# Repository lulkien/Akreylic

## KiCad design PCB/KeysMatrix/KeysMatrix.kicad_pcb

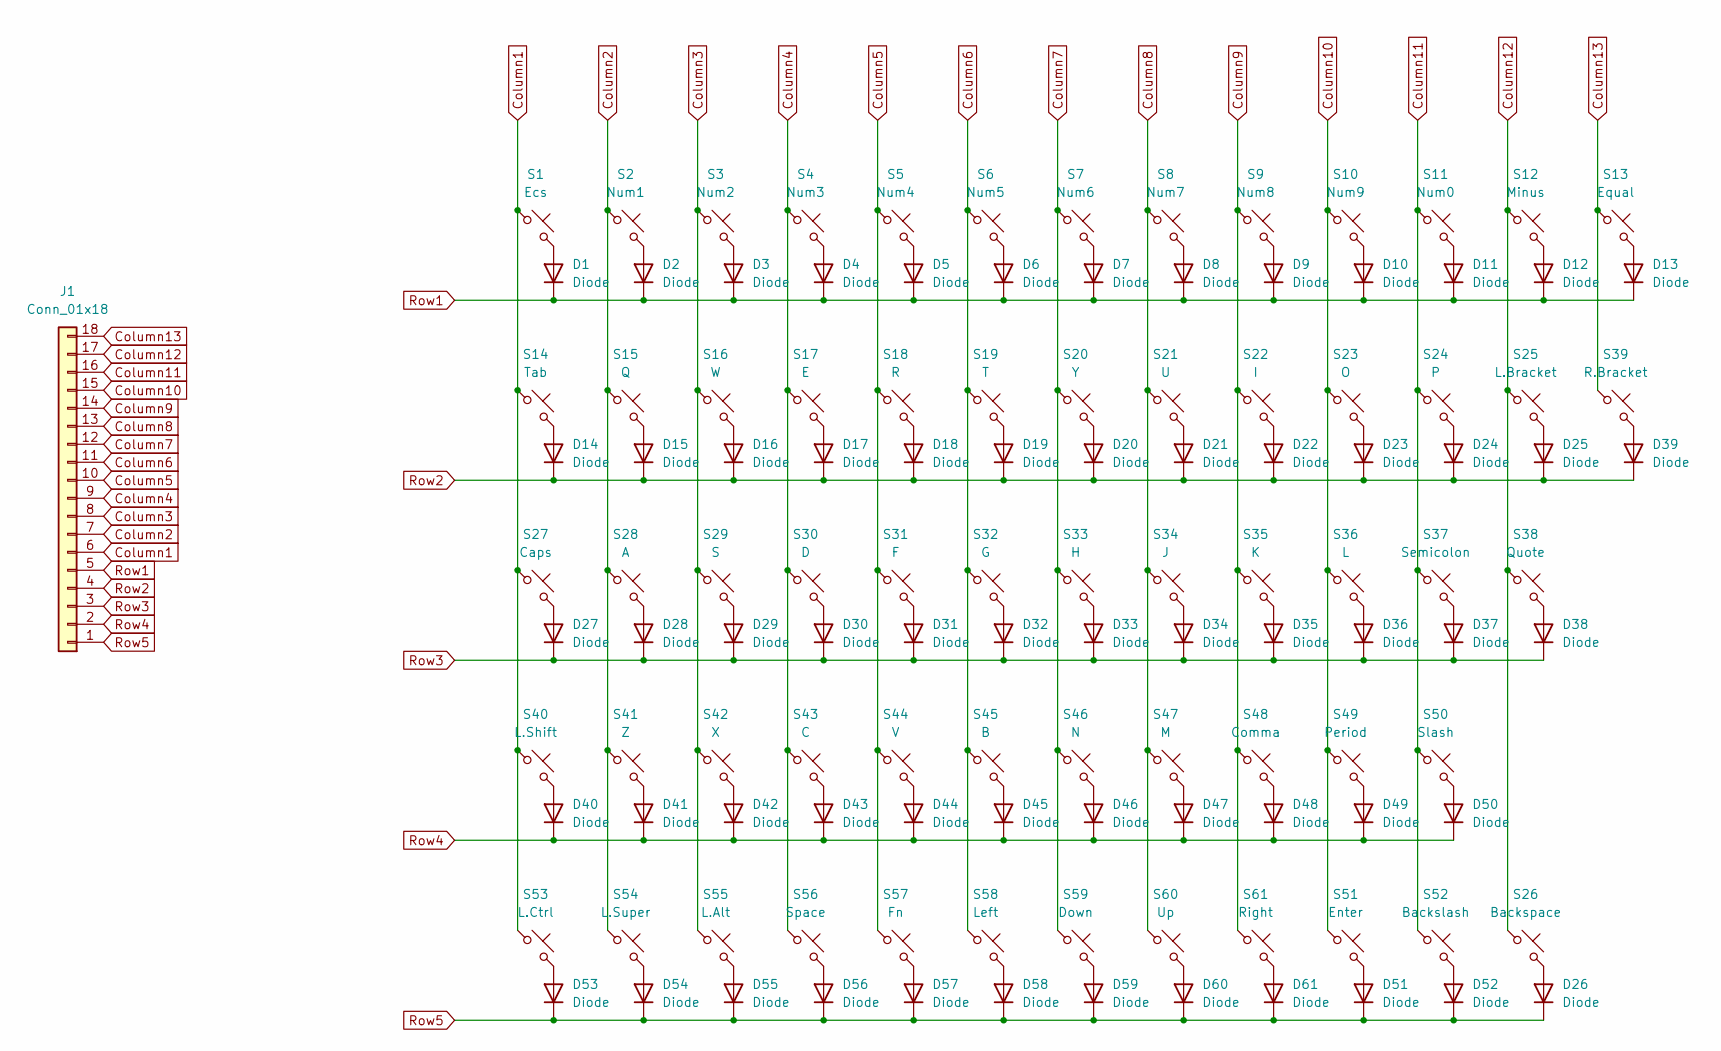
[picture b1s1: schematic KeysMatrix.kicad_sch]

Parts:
D1, D2, D3, D4, D5, D6, D7, D8, D9, D10, D11, D12, D13, D14, D15, D16, D17, D18, D19, D20, D21, D22, D23, D24, D25, D26, D27, D28, D29, D30, D31, D32, D33, D34, D35, D36, D37, D38, D39, D40, D41, D42, D43, D44, D45, D46, D47, D48, D49, D50, D51, D52, D53, D54, D55, D56, D57, D58, D59, D60, D61: Diode; D_SOD-123
J1: Conn_01x18; Hirose_FH12-18S-0.5SH_1x18-1MP_P0.50mm_Horizontal
S1: Ecs; Hotswap_MX_1.00u
S2: Num1; Hotswap_MX_1.00u
S3: Num2; Hotswap_MX_1.00u
S4: Num3; Hotswap_MX_1.00u
S5: Num4; Hotswap_MX_1.00u
S6: Num5; Hotswap_MX_1.00u
S7: Num6; Hotswap_MX_1.00u
S8: Num7; Hotswap_MX_1.00u
S9: Num8; Hotswap_MX_1.00u
S10: Num9; Hotswap_MX_1.00u
S11: Num0; Hotswap_MX_1.00u
S12: Minus; Hotswap_MX_1.00u
S13: Equal; Hotswap_MX_1.00u
S14: Tab; Hotswap_MX_1.50u
S15: Q; Hotswap_MX_1.00u
S16: W; Hotswap_MX_1.00u
S17: E; Hotswap_MX_1.00u
S18: R; Hotswap_MX_1.00u
S19: T; Hotswap_MX_1.00u
S20: Y; Hotswap_MX_1.00u
S21: U; Hotswap_MX_1.00u
S22: I; Hotswap_MX_1.00u
S23: O; Hotswap_MX_1.00u
S24: P; Hotswap_MX_1.00u
S25: L.Bracket; Hotswap_MX_1.00u
S26: Backspace; Hotswap_MX_2.00u
S27: Caps; Hotswap_MX_1.75u
S28: A; Hotswap_MX_1.00u
S29: S; Hotswap_MX_1.00u
S30: D; Hotswap_MX_1.00u
S31: F; Hotswap_MX_1.00u
S32: G; Hotswap_MX_1.00u
S33: H; Hotswap_MX_1.00u
S34: J; Hotswap_MX_1.00u
S35: K; Hotswap_MX_1.00u
S36: L; Hotswap_MX_1.00u
S37: Semicolon; Hotswap_MX_1.00u
S38: Quote; Hotswap_MX_1.00u
S39: R.Bracket; Hotswap_MX_1.00u
S40: L.Shift; Hotswap_MX_2.25u
S41: Z; Hotswap_MX_1.00u
S42: X; Hotswap_MX_1.00u
S43: C; Hotswap_MX_1.00u
S44: V; Hotswap_MX_1.00u
S45: B; Hotswap_MX_1.00u
S46: N; Hotswap_MX_1.00u
S47: M; Hotswap_MX_1.00u
S48: Comma; Hotswap_MX_1.00u
S49: Period; Hotswap_MX_1.00u
S50: Slash; Hotswap_MX_1.00u
S51: Enter; Hotswap_MX_2.25u
S52: Backslash; Hotswap_MX_1.50u
S53: L.Ctrl; Hotswap_MX_1.25u
S54: L.Super; Hotswap_MX_1.25u
S55: L.Alt; Hotswap_MX_1.25u
S56: Space; Hotswap_MX_6.25u
S57: Fn; Hotswap_MX_1.25u
S58: Left; Hotswap_MX_1.00u
S59: Down; Hotswap_MX_1.00u
S60: Up; Hotswap_MX_1.00u
S61: Right; Hotswap_MX_1.00u

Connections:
Column1: J1.6, S1.1, S14.1, S27.1, S40.1, S53.1
Column2: J1.7, S2.1, S15.1, S28.1, S41.1, S54.1
Column3: J1.8, S3.1, S16.1, S29.1, S42.1, S55.1
Column4: J1.9, S4.1, S17.1, S30.1, S43.1, S56.1
Column5: J1.10, S5.1, S18.1, S31.1, S44.1, S57.1
Column6: J1.11, S6.1, S19.1, S32.1, S45.1, S58.1
Column7: J1.12, S7.1, S20.1, S33.1, S46.1, S59.1
Column8: J1.13, S8.1, S21.1, S34.1, S47.1, S60.1
Column9: J1.14, S9.1, S22.1, S35.1, S48.1, S61.1
Column10: J1.15, S10.1, S23.1, S36.1, S49.1, S51.1
Column11: J1.16, S11.1, S24.1, S37.1, S50.1, S52.1
Column12: J1.17, S12.1, S25.1, S26.1, S38.1
Column13: J1.18, S13.1, S39.1
unnamed: D1.2 (A), S1.2
unnamed: D2.2 (A), S2.2
unnamed: D3.2 (A), S3.2
unnamed: D4.2 (A), S4.2
unnamed: D5.2 (A), S5.2
unnamed: D6.2 (A), S6.2
unnamed: D7.2 (A), S7.2
unnamed: D8.2 (A), S8.2
unnamed: D9.2 (A), S9.2
unnamed: D10.2 (A), S10.2
unnamed: D11.2 (A), S11.2
unnamed: D12.2 (A), S12.2
unnamed: D13.2 (A), S13.2
unnamed: D14.2 (A), S14.2
unnamed: D15.2 (A), S15.2
unnamed: D16.2 (A), S16.2
unnamed: D17.2 (A), S17.2
unnamed: D18.2 (A), S18.2
unnamed: D19.2 (A), S19.2
unnamed: D20.2 (A), S20.2
unnamed: D21.2 (A), S21.2
unnamed: D22.2 (A), S22.2
unnamed: D23.2 (A), S23.2
unnamed: D24.2 (A), S24.2
unnamed: D25.2 (A), S25.2
unnamed: D26.2 (A), S26.2
unnamed: D27.2 (A), S27.2
unnamed: D28.2 (A), S28.2
unnamed: D29.2 (A), S29.2
unnamed: D30.2 (A), S30.2
unnamed: D31.2 (A), S31.2
unnamed: D32.2 (A), S32.2
unnamed: D33.2 (A), S33.2
unnamed: D34.2 (A), S34.2
unnamed: D35.2 (A), S35.2
unnamed: D36.2 (A), S36.2
unnamed: D37.2 (A), S37.2
unnamed: D38.2 (A), S38.2
unnamed: D39.2 (A), S39.2
unnamed: D40.2 (A), S40.2
unnamed: D41.2 (A), S41.2
unnamed: D42.2 (A), S42.2
unnamed: D43.2 (A), S43.2
unnamed: D44.2 (A), S44.2
unnamed: D45.2 (A), S45.2
unnamed: D46.2 (A), S46.2
unnamed: D47.2 (A), S47.2
unnamed: D48.2 (A), S48.2
unnamed: D49.2 (A), S49.2
unnamed: D50.2 (A), S50.2
unnamed: D51.2 (A), S51.2
unnamed: D52.2 (A), S52.2
unnamed: D53.2 (A), S53.2
unnamed: D54.2 (A), S54.2
unnamed: D55.2 (A), S55.2
unnamed: D56.2 (A), S56.2
unnamed: D57.2 (A), S57.2
unnamed: D58.2 (A), S58.2
unnamed: D59.2 (A), S59.2
unnamed: D60.2 (A), S60.2
unnamed: D61.2 (A), S61.2
Row1: D1.1 (K), D2.1 (K), D3.1 (K), D4.1 (K), D5.1 (K), D6.1 (K), D7.1 (K), D8.1 (K), D9.1 (K), D10.1 (K), D11.1 (K), D12.1 (K), D13.1 (K), J1.5
Row2: D14.1 (K), D15.1 (K), D16.1 (K), D17.1 (K), D18.1 (K), D19.1 (K), D20.1 (K), D21.1 (K), D22.1 (K), D23.1 (K), D24.1 (K), D25.1 (K), D39.1 (K), J1.4
Row3: D27.1 (K), D28.1 (K), D29.1 (K), D30.1 (K), D31.1 (K), D32.1 (K), D33.1 (K), D34.1 (K), D35.1 (K), D36.1 (K), D37.1 (K), D38.1 (K), J1.3
Row4: D40.1 (K), D41.1 (K), D42.1 (K), D43.1 (K), D44.1 (K), D45.1 (K), D46.1 (K), D47.1 (K), D48.1 (K), D49.1 (K), D50.1 (K), J1.2
Row5: D26.1 (K), D51.1 (K), D52.1 (K), D53.1 (K), D54.1 (K), D55.1 (K), D56.1 (K), D57.1 (K), D58.1 (K), D59.1 (K), D60.1 (K), D61.1 (K), J1.1

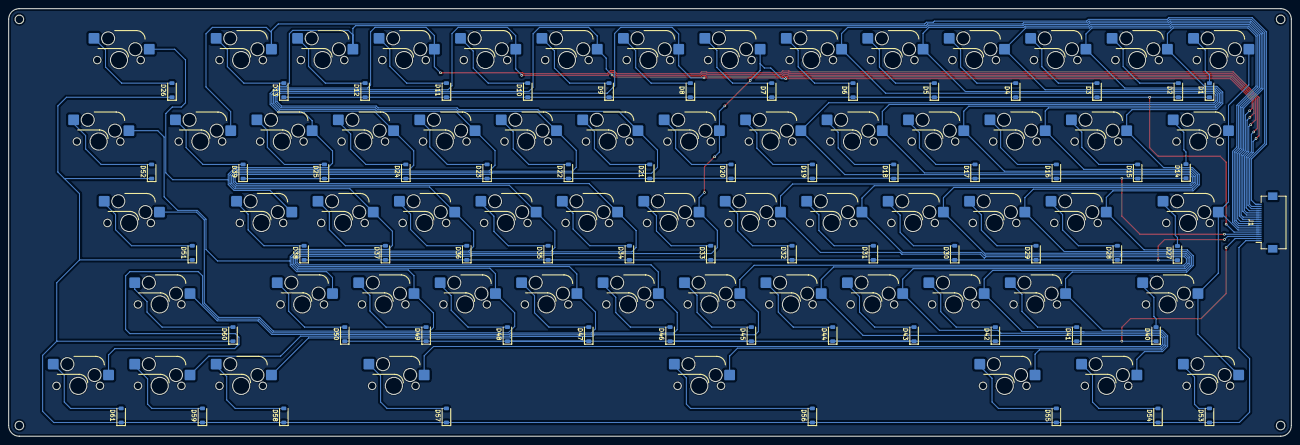
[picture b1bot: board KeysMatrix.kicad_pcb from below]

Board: 2 copper layers, 300.0 x 100.0 mm, 123 parts (62 on the bottom side), 79 nets.

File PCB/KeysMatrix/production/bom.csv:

Designator,Footprint,Quantity,Value,LCSC Part #
"D1, D10, D11, D12, D13, D14, D15, D16, D17, D18, D19, D2, D20, D21, D22, D23, D24, D25, D26, D27, D28, D29, D3, D30, D31, D32, D33, D34, D35, D36, D37, D38, D39, D4, D40, D41, D42, D43, D44, D45, D46, D47, D48, D49, D5, D50, D51, D52, D53, D54, D55, D56, D57, D58, D59, D6, D60, D61, D7, D8, D9",D_SOD-123,61,Diode,C2099
J1,Hirose_FH12-18S-0.5SH_1x18-1MP_P0.50mm_Horizontal,1,Conn_01x18,C2856802

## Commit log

2024-10-13 Design PCB
2024-10-13 Add keyboard layout design
2024-10-14 Complete KeysMatrix
2024-10-14 Add production files
2024-10-14 Add controller module
